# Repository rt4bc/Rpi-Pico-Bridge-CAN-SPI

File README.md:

# CAN to SPI Controller Based on MCP2518FD and Raspberry Pi Pico

## Description

This project is a CAN-to-SPI controller built using the MCP2518FD CAN controller and the Raspberry Pi Pico (RP2040). It allows communication between CAN and SPI-enabled devices, making it useful for embedded applications, automotive networks, and industrial control systems.

RP2040's SPI1&I2C1 defaualt configured as a controller, which make it possbile bridge the CAN bus and other SPI&I2C peripherals.

## Features
- Built with Raspberry Pi Pico (RP2040) and MCP2518FD
- RP2040 SPI1 as SPI controller which can communicate with mikro interface
- RP2040 SPI0 as SPI controller which works with MCP2518FD
- CAN FD support (up to 8 Mbps)
- Supports standard and extended CAN IDs
- Configurable bit rates and filters

## Hardware Requirements

- Raspberry Pi Pico (RP2040)
- MCP2518FD CAN controller with SPI interface
- Power supply (3.3V/5V depending on CAN transceiver)
- Optional: CAN bus terminator (120Ω)

## Software Setup

1. Clone this fw repository.
2. Use PC GUI 

## Usage

Send SPI commands to the Pico, which will translate and forward them to the CAN bus via MCP2518FD. Incoming CAN messages are forwarded back to the host via SPI.

## TODO

- CAN Bus GUI Tools
- USB configure tools

---

# 基于 MCP2518FD 和 Raspberry Pi Pico 的 CAN 转 SPI 控制器

## 项目简介

本项目基于 MCP2518FD CAN 控制器和 Raspberry Pi Pico（RP2040）实现了一个 CAN 到 SPI 的通信控制器。该控制器可以实现 CAN 与 SPI 设备之间的通信，广泛适用于嵌入式系统、汽车网络以及工业控制系统。

## 功能特点

- 支持 CAN FD（速率最高达 8 Mbps）
- SPI 接口连接主控系统
- 支持标准帧和扩展帧格式
- 可配置的波特率与过滤器
- 采用 Raspberry Pi Pico 和 MCP2518FD 芯片

## 硬件需求

- Raspberry Pi Pico（RP2040）
- MCP2518FD（SPI接口）
- 电源（3.3V 或 5V，视 CAN 收发器而定）
- 可选：CAN 总线终端电阻（120Ω）

## 软件配置

1. 克隆本项目代码。
3. 将主控设备通过 SPI 接口连接到 Pico。
4. 使用 SPI 库与 Pico 通信并发送/接收 CAN 消息。

## 使用说明

主控系统通过 SPI 向 Pico 发送命令，Pico 再通过 MCP2518FD 将其转发至 CAN 总线。同时，CAN 总线接收到的数据也会被 Pico 通过 SPI 回传至主控系统。

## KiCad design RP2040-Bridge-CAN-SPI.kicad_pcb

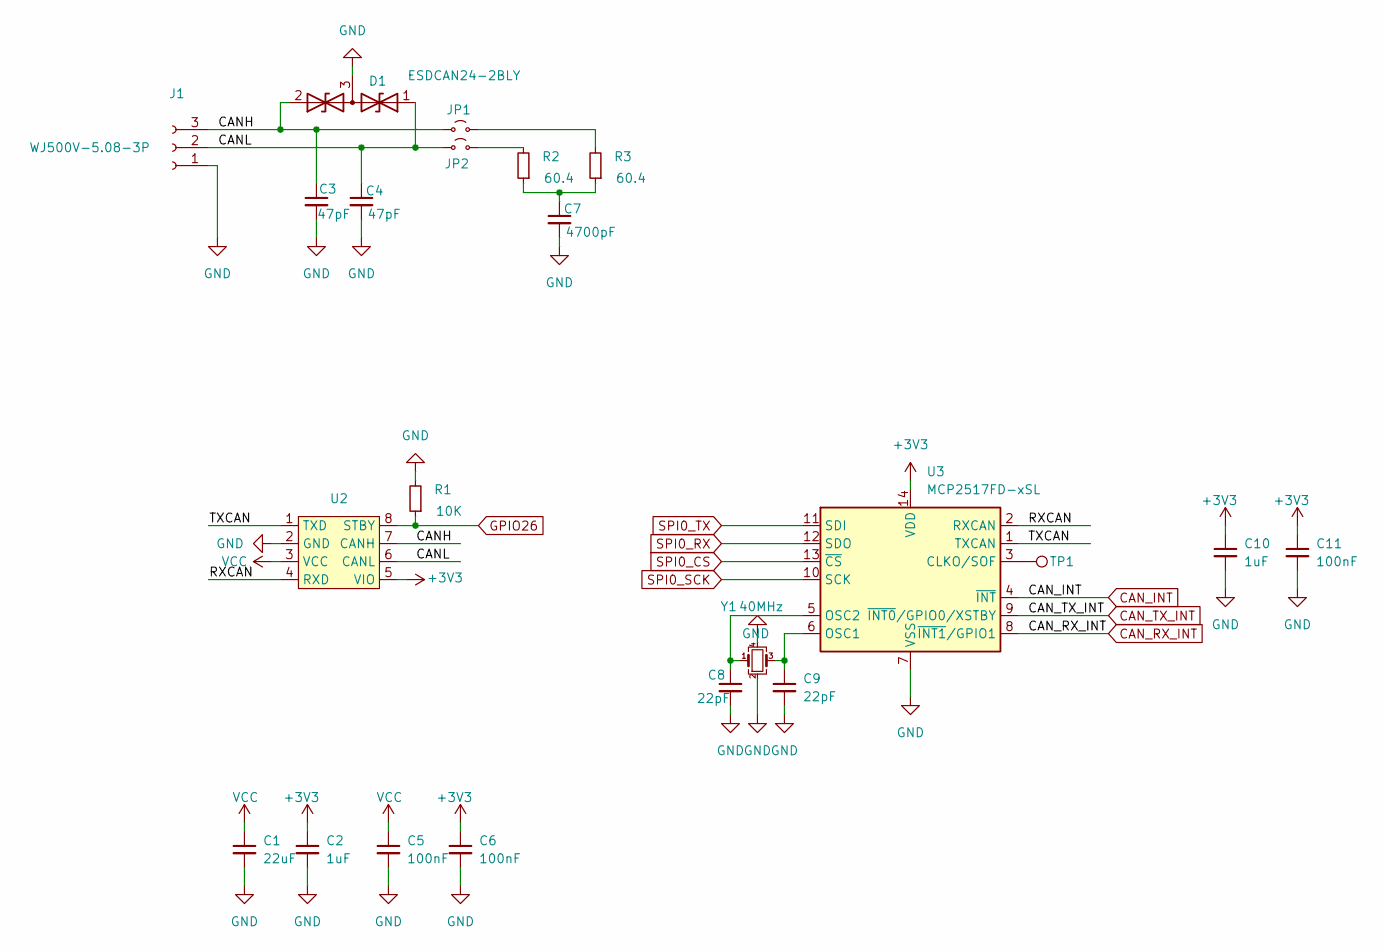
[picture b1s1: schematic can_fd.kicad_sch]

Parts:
C1: 22uF; C_0805_2012Metric_Pad1.18x1.45mm_HandSolder
C2, C10: 1uF; C_0603_1608Metric_Pad1.08x0.95mm_HandSolder
C3, C4: 47pF; C_0603_1608Metric_Pad1.08x0.95mm_HandSolder
C5, C6, C11: 100nF; C_0603_1608Metric_Pad1.08x0.95mm_HandSolder
C7: 4700pF; C_0603_1608Metric_Pad1.08x0.95mm_HandSolder
C8, C9: 22pF; C_0603_1608Metric_Pad1.08x0.95mm_HandSolder
D1: ESDCAN24-2BLY; SOT-23-3
J1: Conn_01x03_Socket; TerminalBlock_bornier-3_P5.08mm
JP1, JP2: Jumper_2_Small_Open; PinHeader_1x02_P2.00mm_Vertical
R1: 10K; R_0603_1608Metric_Pad0.98x0.95mm_HandSolder
R2, R3: 60.4; R_0603_1608Metric_Pad0.98x0.95mm_HandSolder
TP1: TestPoint; TestPoint_Pad_D1.0mm
U2: High-speed CAN FD Transceiver with Standby Mode a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; SOIC-8_3.9x4.9mm_P1.27mm
U3: MCP2517FD-xSL; SOIC-14_3.9x8.7mm_P1.27mm
Y1: 40MHz; Crystal_SMD_SeikoEpson_TSX3225-4Pin_3.2x2.5mm

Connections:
+3V3: C2.1, C6.1, C10.1, C11.1, U2.5 (VIO), U3.14 (VDD); also elsewhere on the board
/CAN-FD-Interface/CANH: C3.1, D1.2 (A2), J1.3, JP1.1 (A), U2.7 (CANH)
/CAN-FD-Interface/CANL: C4.1, D1.1 (A1), J1.2, JP2.1 (A), U2.6 (CANL)
/CAN-FD-Interface/RXCAN: U2.4 (RXD), U3.2 (RXCAN)
/CAN-FD-Interface/TXCAN: U2.1 (TXD), U3.1 (TXCAN)
CAN_INT: U3.4 (~INT); also elsewhere on the board
CAN_RX_INT: U3.8 (~INT1/GPIO1); also elsewhere on the board
CAN_TX_INT: U3.9 (~INT0/GPIO0/XSTBY); also elsewhere on the board
GND: C1.2, C2.2, C3.2, C4.2, C5.2, C6.2, C7.2, C8.2, C9.2, C10.2, C11.2, D1.3 (common), J1.1, R1.2, U2.2 (GND), U3.7 (VSS), Y1.2, Y1.4; also elsewhere on the board
GPIO26: R1.1, U2.8 (STBY); also elsewhere on the board
unnamed: C7.1, R2.1, R3.1
unnamed: JP1.2 (B), R3.2
unnamed: JP2.2 (B), R2.2
unnamed: TP1.1, U3.3 (CLKO/SOF)
unnamed: C9.1, U3.6 (OSC1), Y1.3
unnamed: C8.1, U3.5 (OSC2), Y1.1
SPI0_CS: U3.13 (~CS); also elsewhere on the board
SPI0_RX: U3.12 (SDO); also elsewhere on the board
SPI0_SCK: U3.10 (SCK); also elsewhere on the board
SPI0_TX: U3.11 (SDI); also elsewhere on the board
VCC: C1.1, C5.1, U2.3 (VCC); also elsewhere on the board

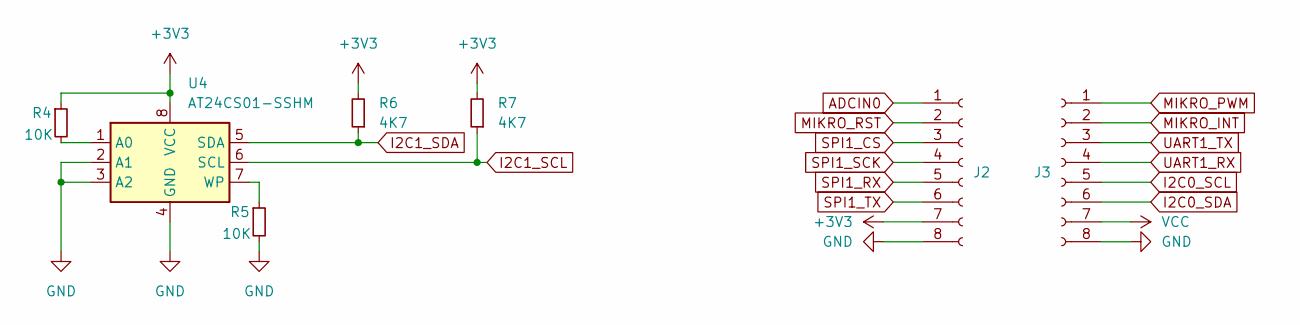
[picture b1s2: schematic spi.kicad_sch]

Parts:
J2, J3: Conn_01x08_Socket; PinSocket_1x08_P2.54mm_Vertical
R4, R5: 10K; R_0603_1608Metric_Pad0.98x0.95mm_HandSolder
R6, R7: 4K7; R_0603_1608Metric_Pad0.98x0.95mm_HandSolder
U4: AT24CS01-SSHM; SOIC-8_3.9x4.9mm_P1.27mm

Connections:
+3V3: J2.7, R4.1, R6.2, R7.2, U4.8 (VCC); also elsewhere on the board
ADCIN0: J2.1
GND: J2.8, J3.8, R5.2, U4.2 (A1), U4.3 (A2), U4.4 (GND); also elsewhere on the board
I2C0_SCL: J3.5; also elsewhere on the board
I2C0_SDA: J3.6; also elsewhere on the board
I2C1_SCL: R7.1, U4.6 (SCL); also elsewhere on the board
I2C1_SDA: R6.1, U4.5 (SDA); also elsewhere on the board
MIKRO_INT: J3.2; also elsewhere on the board
MIKRO_PWM: J3.1; also elsewhere on the board
MIKRO_RST: J2.2; also elsewhere on the board
unnamed: R4.2, U4.1 (A0)
unnamed: R5.1, U4.7 (WP)
SPI1_CS: J2.3; also elsewhere on the board
SPI1_RX: J2.5; also elsewhere on the board
SPI1_SCK: J2.4; also elsewhere on the board
SPI1_TX: J2.6; also elsewhere on the board
UART1_RX: J3.4; also elsewhere on the board
UART1_TX: J3.3; also elsewhere on the board
VCC: J3.7; also elsewhere on the board

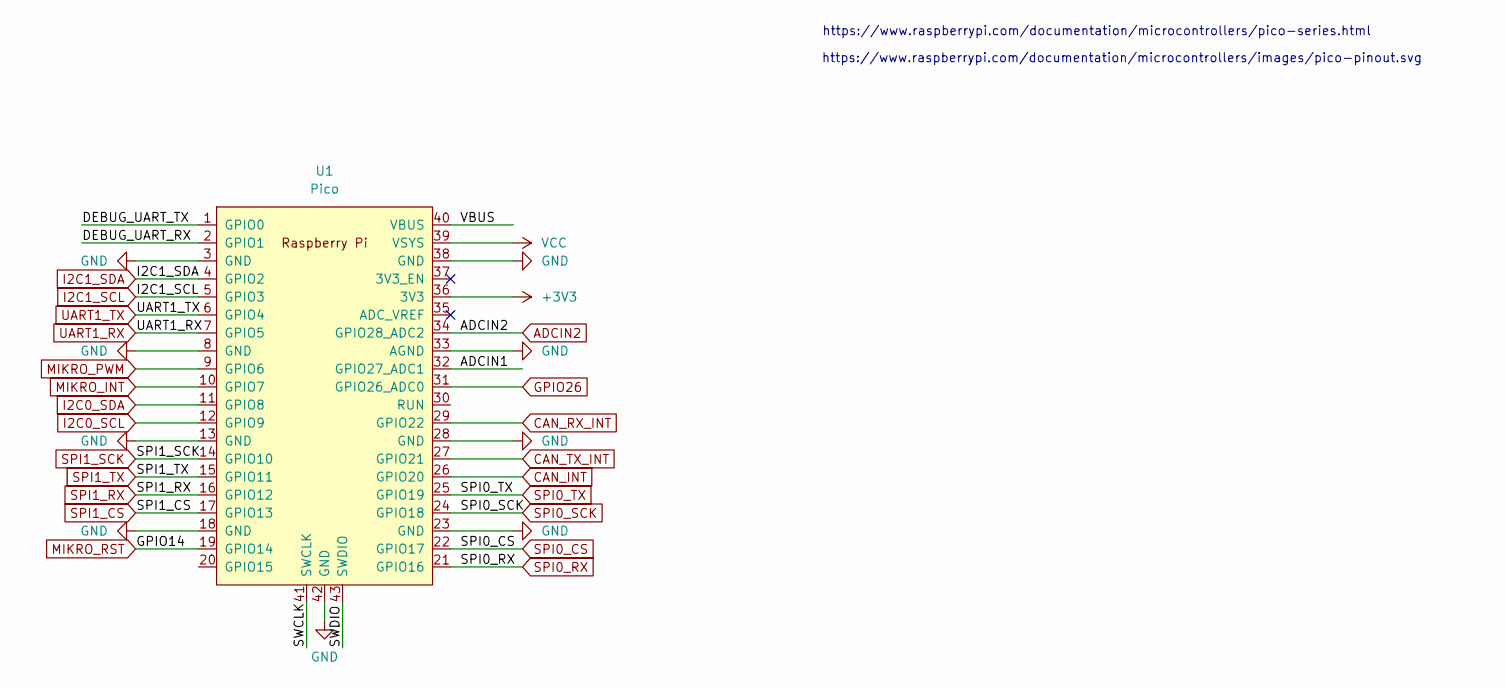
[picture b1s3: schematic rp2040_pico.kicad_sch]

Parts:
U1: Pico; RPi_Pico_SMD_TH

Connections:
+3V3: U1.36 (3V3); also elsewhere on the board
/RP2040-Pico/ADCIN1: U1.32 (GPIO27_ADC1)
/RP2040-Pico/DEBUG_UART_RX: U1.2 (GPIO1)
/RP2040-Pico/DEBUG_UART_TX: U1.1 (GPIO0)
/RP2040-Pico/SWCLK: U1.41 (SWCLK)
/RP2040-Pico/SWDIO: U1.43 (SWDIO)
/RP2040-Pico/VBUS: U1.40 (VBUS)
ADCIN2: U1.34 (GPIO28_ADC2)
CAN_INT: U1.26 (GPIO20); also elsewhere on the board
CAN_RX_INT: U1.29 (GPIO22); also elsewhere on the board
CAN_TX_INT: U1.27 (GPIO21); also elsewhere on the board
GND: U1.3 (GND), U1.8 (GND), U1.13 (GND), U1.18 (GND), U1.23 (GND), U1.28 (GND), U1.33 (AGND), U1.38 (GND), U1.42 (GND); also elsewhere on the board
GPIO26: U1.31 (GPIO26_ADC0); also elsewhere on the board
I2C0_SCL: U1.12 (GPIO9); also elsewhere on the board
I2C0_SDA: U1.11 (GPIO8); also elsewhere on the board
I2C1_SCL: U1.5 (GPIO3); also elsewhere on the board
I2C1_SDA: U1.4 (GPIO2); also elsewhere on the board
MIKRO_INT: U1.10 (GPIO7); also elsewhere on the board
MIKRO_PWM: U1.9 (GPIO6); also elsewhere on the board
MIKRO_RST: U1.19 (GPIO14); also elsewhere on the board
SPI0_CS: U1.22 (GPIO17); also elsewhere on the board
SPI0_RX: U1.21 (GPIO16); also elsewhere on the board
SPI0_SCK: U1.24 (GPIO18); also elsewhere on the board
SPI0_TX: U1.25 (GPIO19); also elsewhere on the board
SPI1_CS: U1.17 (GPIO13); also elsewhere on the board
SPI1_RX: U1.16 (GPIO12); also elsewhere on the board
SPI1_SCK: U1.14 (GPIO10); also elsewhere on the board
SPI1_TX: U1.15 (GPIO11); also elsewhere on the board
UART1_RX: U1.7 (GPIO5); also elsewhere on the board
UART1_TX: U1.6 (GPIO4); also elsewhere on the board
VCC: U1.39 (VSYS); also elsewhere on the board

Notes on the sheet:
https://www.raspberrypi.com/documentation/microcontrollers/pico-series.html
https://www.raspberrypi.com/documentation/microcontrollers/images/pico-pinout.svg

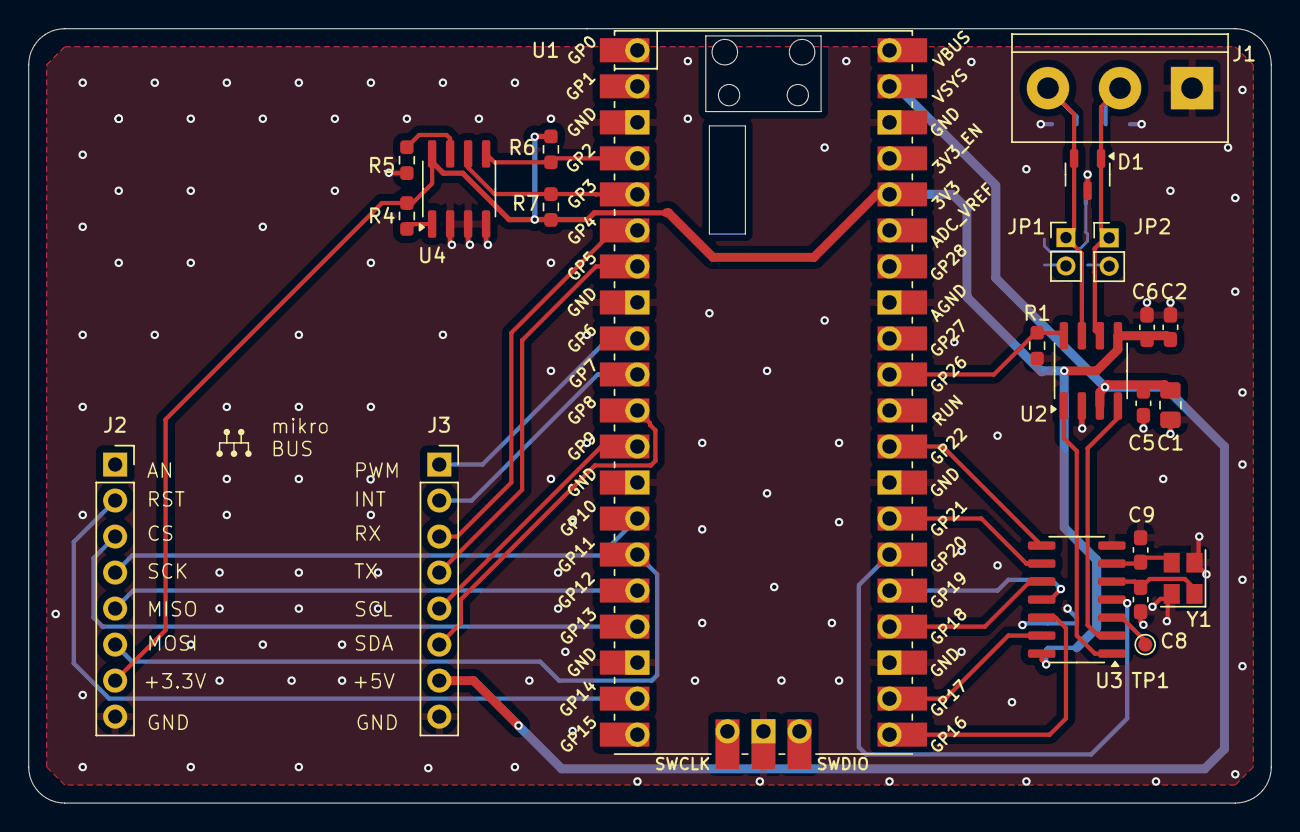
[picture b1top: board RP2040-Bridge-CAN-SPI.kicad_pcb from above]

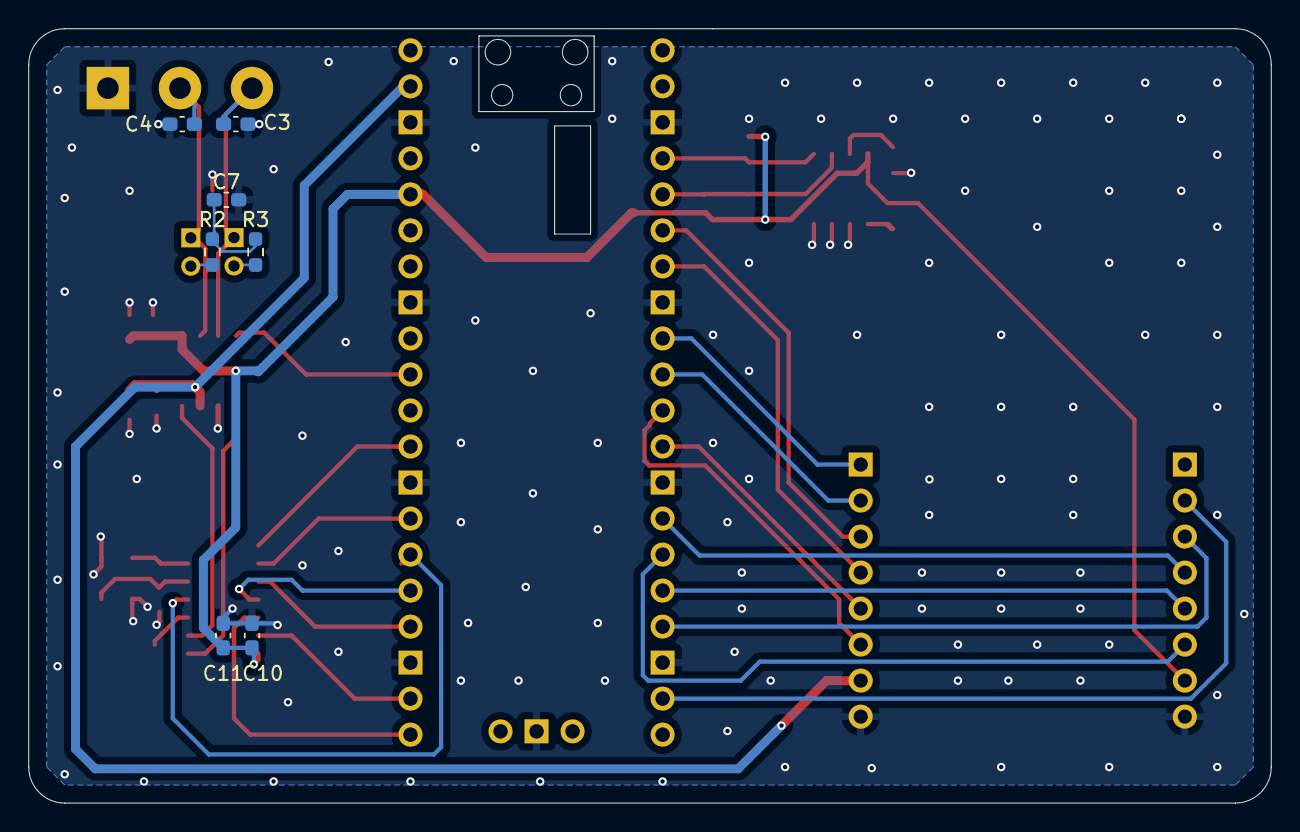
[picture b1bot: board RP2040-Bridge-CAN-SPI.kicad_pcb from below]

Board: 2 copper layers, 87.6 x 54.6 mm, 30 parts (7 on the bottom side), 36 nets.

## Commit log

2025-04-13 Create LICENSE
2025-04-19 update design
2025-04-19 udpate readme & pcb png pics
2025-04-19 udpate readme
2025-06-24 update comments docs
2025-06-26 update comments
